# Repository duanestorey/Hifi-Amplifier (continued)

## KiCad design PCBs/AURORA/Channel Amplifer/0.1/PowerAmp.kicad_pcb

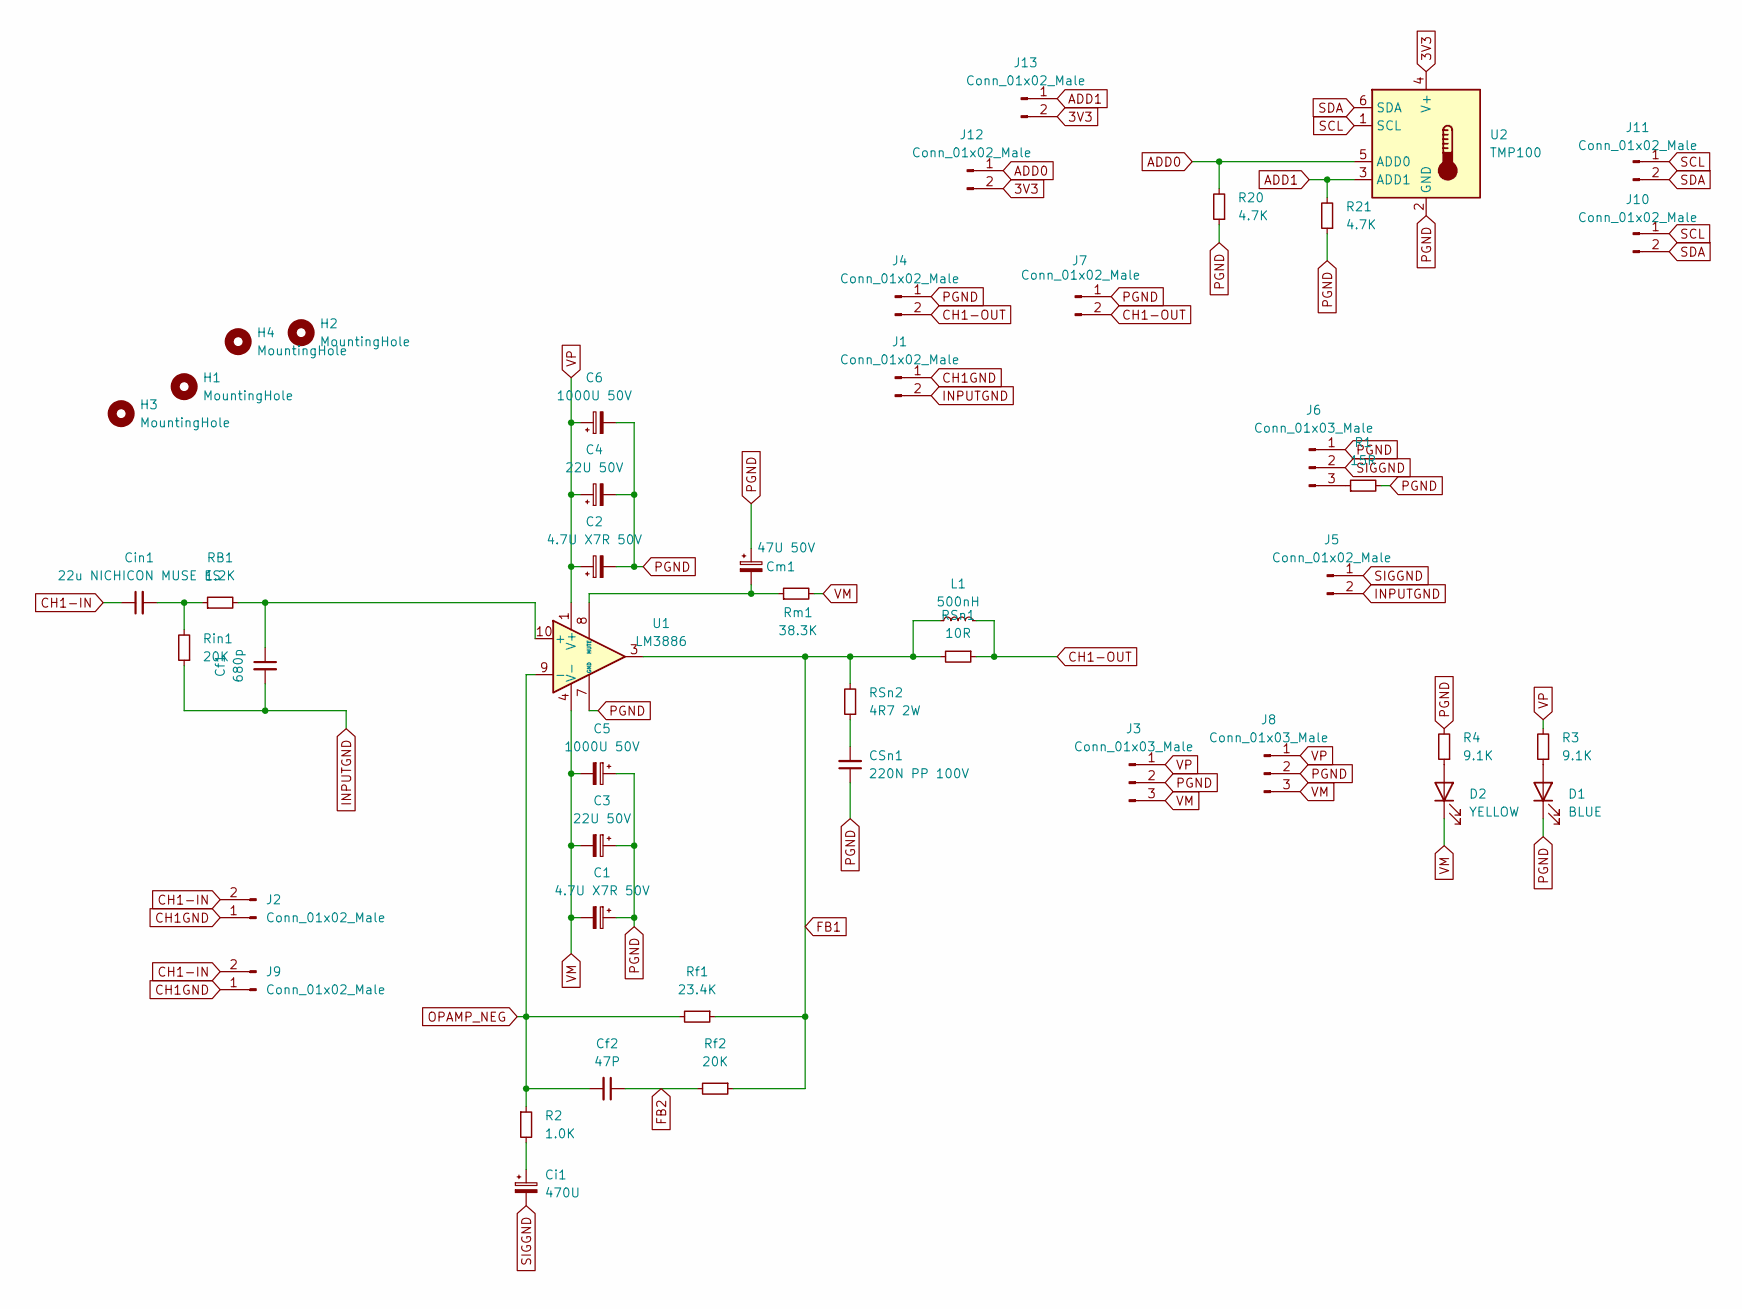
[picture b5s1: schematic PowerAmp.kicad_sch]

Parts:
C1, C2: 4.7U X7R 50V; C_1206_3216Metric_Pad1.33x1.80mm_HandSolder
C3, C4: 22U 50V; CP_Radial_D6.3mm_P2.50mm
C5, C6: 1000U 50V; CP_Radial_D12.5mm_P5.00mm
CSn1: 220N PP 100V; C_Rect_L18.0mm_W7.0mm_P15.00mm_FKS3_FKP3
Cf1: 680p; C_1206_3216Metric_Pad1.33x1.80mm_HandSolder
Cf2: 47P; C_1206_3216Metric_Pad1.33x1.80mm_HandSolder
Ci1: 470U; CP_Radial_D12.5mm_P5.00mm
Cin1: 22u NICHICON MUSE ES; C_Radial_D10.0mm_H12.5mm_P5.00mm
Cm1: 47U 50V; CP_Radial_D6.3mm_P2.50mm
D1: BLUE; LED_0805_2012Metric_Pad1.15x1.40mm_HandSolder
D2: YELLOW; LED_0805_2012Metric_Pad1.15x1.40mm_HandSolder
H1, H2, H3, H4: MountingHole; MountingHole_3mm
J1, J5, J12, J13: Conn_01x02_Male; PinHeader_1x02_P2.54mm_Vertical
J2, J9, J10, J11: Conn_01x02_Male; JST_PH_B2B-PH-K_1x02_P2.00mm_Vertical
J3, J8: Conn_01x03_Male; JST_VH_B3P-VH-B_1x03_P3.96mm_Vertical
J4, J7: Conn_01x02_Male; JST_VH_B2P-VH_1x02_P3.96mm_Vertical
J6: Conn_01x03_Male; PinHeader_1x03_P2.54mm_Vertical
L1: 500nH; 500nH Inductor Aliexpress Air Gap
R1: 15R; R_1206_3216Metric_Pad1.30x1.75mm_HandSolder
R2: 1.0K; R_1206_3216Metric_Pad1.30x1.75mm_HandSolder
R3, R4: 9.1K; R_0805_2012Metric_Pad1.20x1.40mm_HandSolder
R20, R21: 4.7K; R_0603_1608Metric_Pad0.98x0.95mm_HandSolder
RB1: 1.2K; R_1206_3216Metric_Pad1.30x1.75mm_HandSolder
RSn1: 10R; R_4020_10251Metric_Pad1.65x5.30mm_HandSolder
RSn2: 4R7 2W; R_2512_6332Metric_Pad1.40x3.35mm_HandSolder
Rf1: 23.4K; R_1206_3216Metric_Pad1.30x1.75mm_HandSolder
Rf2: 20K; R_1206_3216Metric_Pad1.30x1.75mm_HandSolder
Rin1: 20K; R_1206_3216Metric_Pad1.30x1.75mm_HandSolder
Rm1: 38.3K; R_1206_3216Metric_Pad1.30x1.75mm_HandSolder
U1: LM3886; TO-220-11_P3.4x5.08mm_StaggerOdd_Lead4.85mm_Vertical
U2: TMP100; SOT-23-6

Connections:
3V3: J12.2, J13.2, U2.4 (V+)
ADD0: J12.1, R20.2, U2.5 (ADD0)
ADD1: J13.1, R21.2, U2.3 (ADD1)
CH1-IN: Cin1.1, J2.2, J9.2
CH1-OUT: J4.2, J7.2, L1.2, RSn1.1
CH1GND: J1.1, J2.1, J9.1
FB1: L1.1, RSn1.2, RSn2.2, Rf1.1, Rf2.1, U1.3
FB2: Cf2.1, Rf2.2
INPUTGND: Cf1.2, J1.2, J5.2, Rin1.1
unnamed: CSn1.2, RSn2.1
unnamed: Ci1.1, R2.2
unnamed: Cin1.2, RB1.1, Rin1.2
unnamed: D1.2 (A), R3.1
unnamed: D2.2 (A), R4.1
unnamed: J6.3, R1.1
unnamed: Cf1.1, RB1.2, U1.10 (+)
unnamed: Cm1.2, Rm1.1, U1.8 (MUTE)
OPAMP_NEG: Cf2.2, R2.1, Rf1.2, U1.9 (-)
PGND: C1.1, C2.2, C3.1, C4.2, C5.1, C6.2, CSn1.1, Cm1.1, D1.1 (K), J3.2, J4.1, J6.1, J7.1, J8.2, R1.2, R4.2, R20.1, R21.1, U1.7 (GND), U2.2 (GND)
SCL: J10.1, J11.1, U2.1 (SCL)
SDA: J10.2, J11.2, U2.6 (SDA)
SIGGND: Ci1.2, J5.1, J6.2
VM: C1.2, C3.2, C5.2, D2.1 (K), J3.3, J8.3, Rm1.2, U1.4 (V-)
VP: C2.1, C4.1, C6.1, J3.1, J8.1, R3.2, U1.1 (V+), U1.5 (V+)

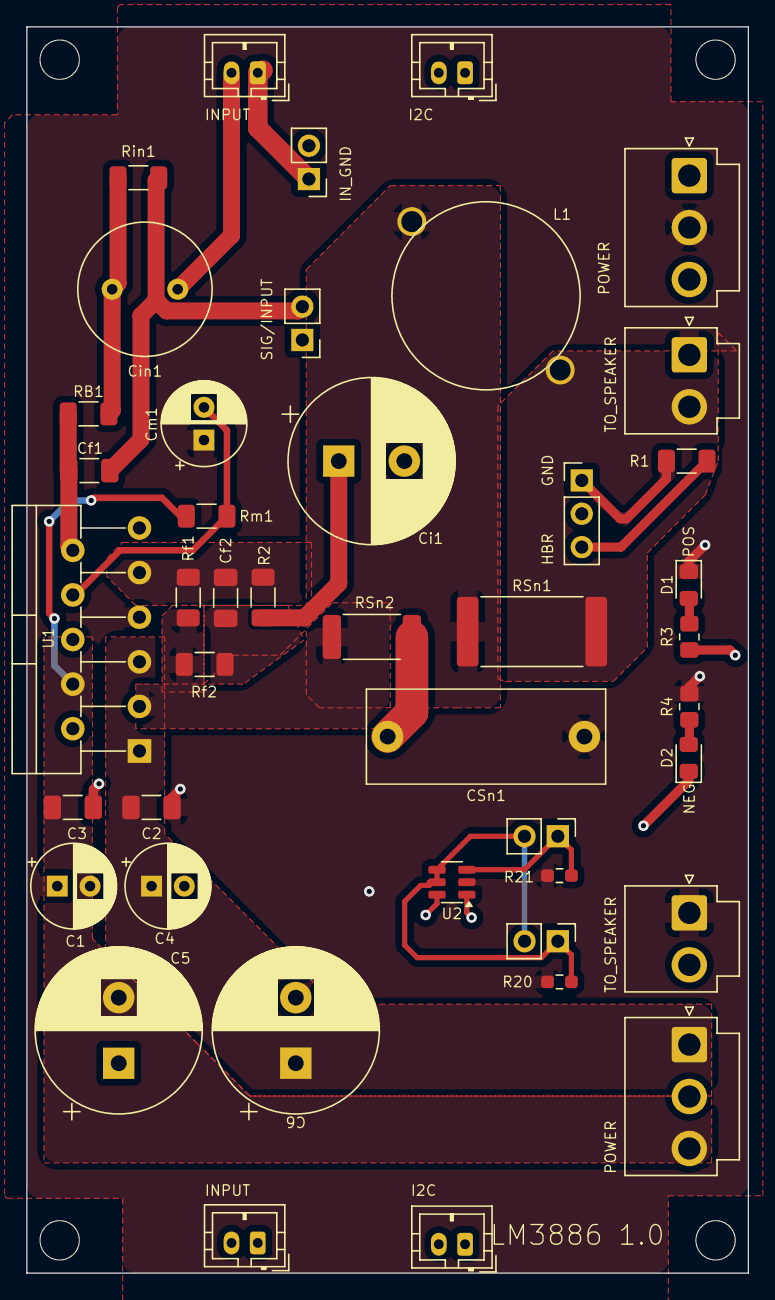
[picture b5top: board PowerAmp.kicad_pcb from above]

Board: 4 copper layers, 55.0 x 95.0 mm, 47 parts (0 on the bottom side), 24 nets.

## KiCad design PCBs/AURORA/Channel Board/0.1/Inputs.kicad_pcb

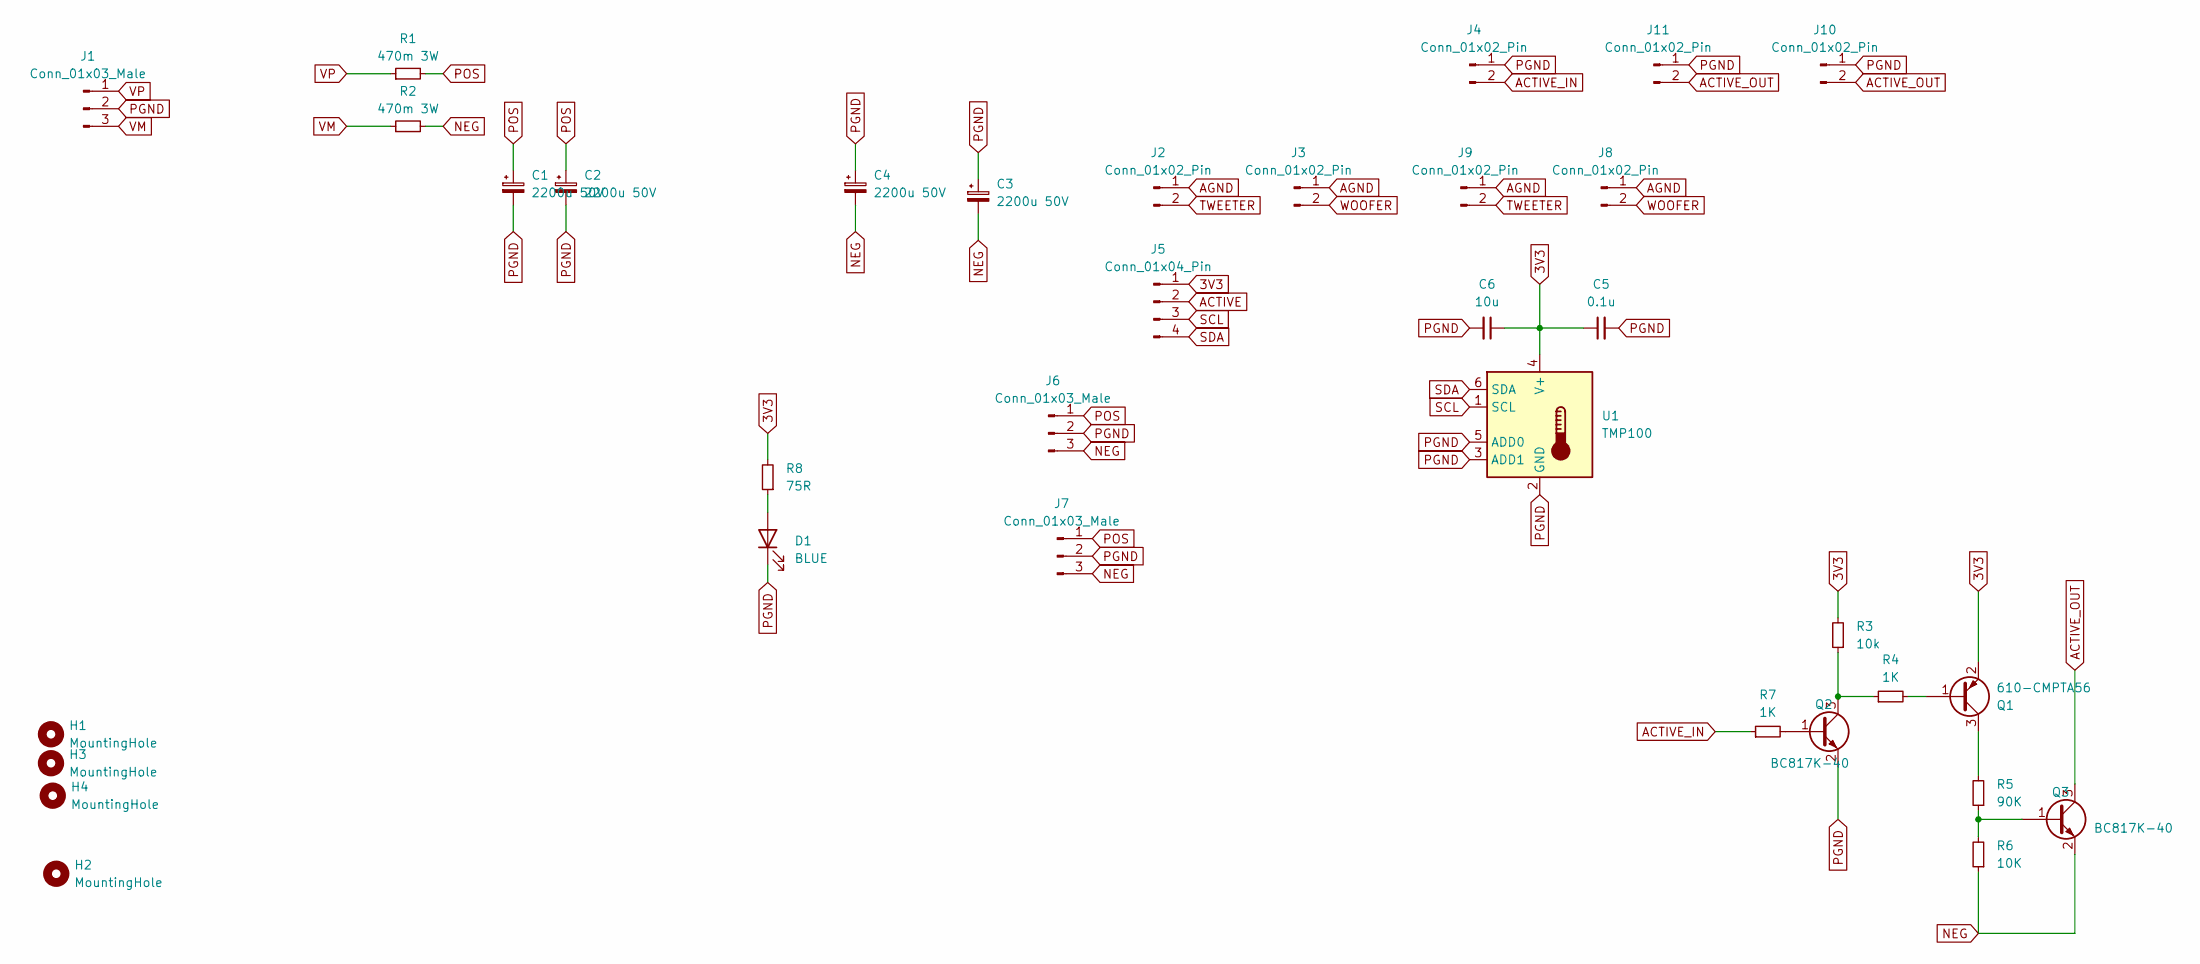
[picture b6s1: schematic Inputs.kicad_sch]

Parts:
C1, C2, C3, C4: 2200u 50V; CP_Radial_D16.0mm_P7.50mm
C5: 0.1u; C_0805_2012Metric_Pad1.18x1.45mm_HandSolder
C6: 10u; C_1206_3216Metric_Pad1.33x1.80mm_HandSolder
D1: BLUE; LED_0805_2012Metric
H1, H2, H3, H4: MountingHole; MountingHole_3.2mm_M3
J1, J6, J7: Conn_01x03_Male; JST_VH_B3P-VH-B_1x03_P3.96mm_Vertical
J2, J3, J4, J8, J9, J10, J11: Conn_01x02_Pin; JST_PH_B2B-PH-K_1x02_P2.00mm_Vertical
J5: Conn_01x04_Pin; JST_PH_B4B-PH-K_1x04_P2.00mm_Vertical
Q1: 610-CMPTA56; TSOT-23
Q2, Q3: BC817K-40; TSOT-23
R1, R2: 470m 3W; R_1218_3246Metric_Pad1.22x4.75mm_HandSolder; Mouser RLW73PA3FR47TDF
R3: 10k; R_0603_1608Metric_Pad0.98x0.95mm_HandSolder
R4, R7: 1K; R_0603_1608Metric_Pad0.98x0.95mm_HandSolder
R5: 90K; R_0603_1608Metric_Pad0.98x0.95mm_HandSolder
R6: 10K; R_0603_1608Metric_Pad0.98x0.95mm_HandSolder
R8: 75R; R_0603_1608Metric_Pad0.98x0.95mm_HandSolder
U1: TMP100; SOT-23-6

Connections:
3V3: C5.1, C6.1, J5.1, Q1.2 (E), R3.2, R8.2, U1.4 (V+)
ACTIVE: J5.2
ACTIVE_IN: J4.2, R7.1
ACTIVE_OUT: J10.2, J11.2, Q3.3 (C)
AGND: J2.1, J3.1, J8.1, J9.1
NEG: C3.2, C4.2, J6.3, J7.3, Q3.2 (E), R2.2, R6.1
unnamed: D1.2 (A), R8.1
unnamed: Q1.1 (B), R4.2
unnamed: Q1.3 (C), R5.2
unnamed: Q2.1 (B), R7.2
unnamed: Q2.3 (C), R3.1, R4.1
unnamed: Q3.1 (B), R5.1, R6.2
PGND: C1.2, C2.2, C3.1, C4.1, C5.2, C6.2, D1.1 (K), J1.2, J4.1, J6.2, J7.2, J10.1, J11.1, Q2.2 (E), U1.2 (GND), U1.3 (ADD1), U1.5 (ADD0)
POS: C1.1, C2.1, J6.1, J7.1, R1.2
SCL: J5.3, U1.1 (SCL)
SDA: J5.4, U1.6 (SDA)
TWEETER: J2.2, J9.2
VM: J1.3, R2.1
VP: J1.1, R1.1
WOOFER: J3.2, J8.2

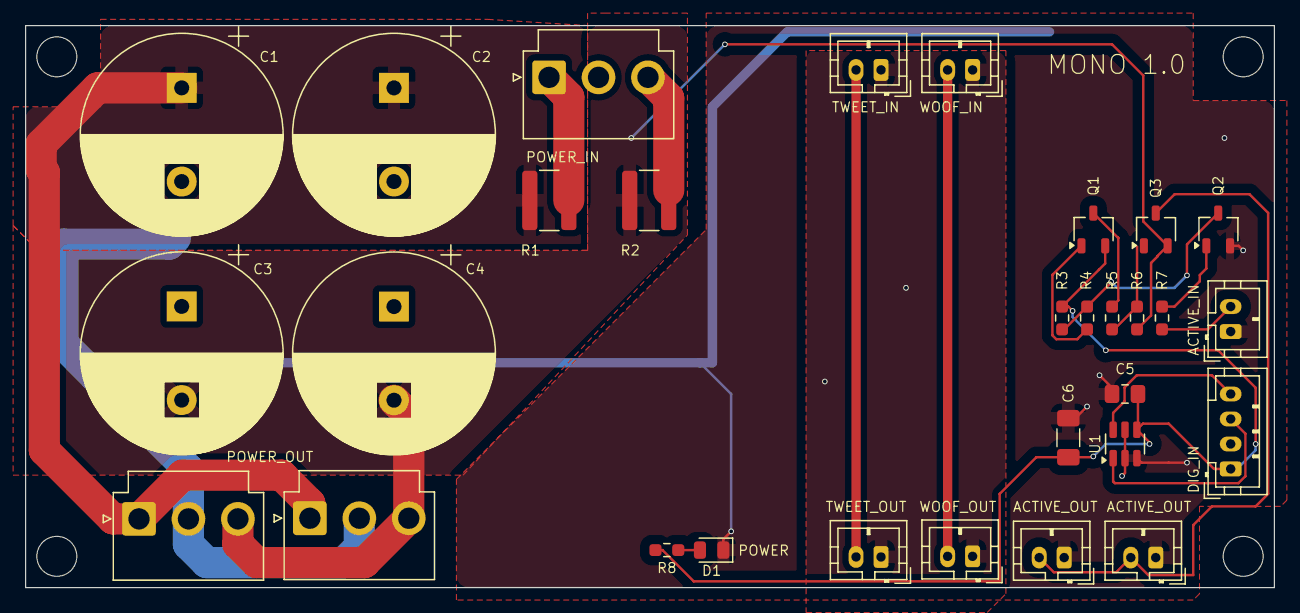
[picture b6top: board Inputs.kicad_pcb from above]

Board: 2 copper layers, 100.0 x 45.0 mm, 34 parts (0 on the bottom side), 19 nets.

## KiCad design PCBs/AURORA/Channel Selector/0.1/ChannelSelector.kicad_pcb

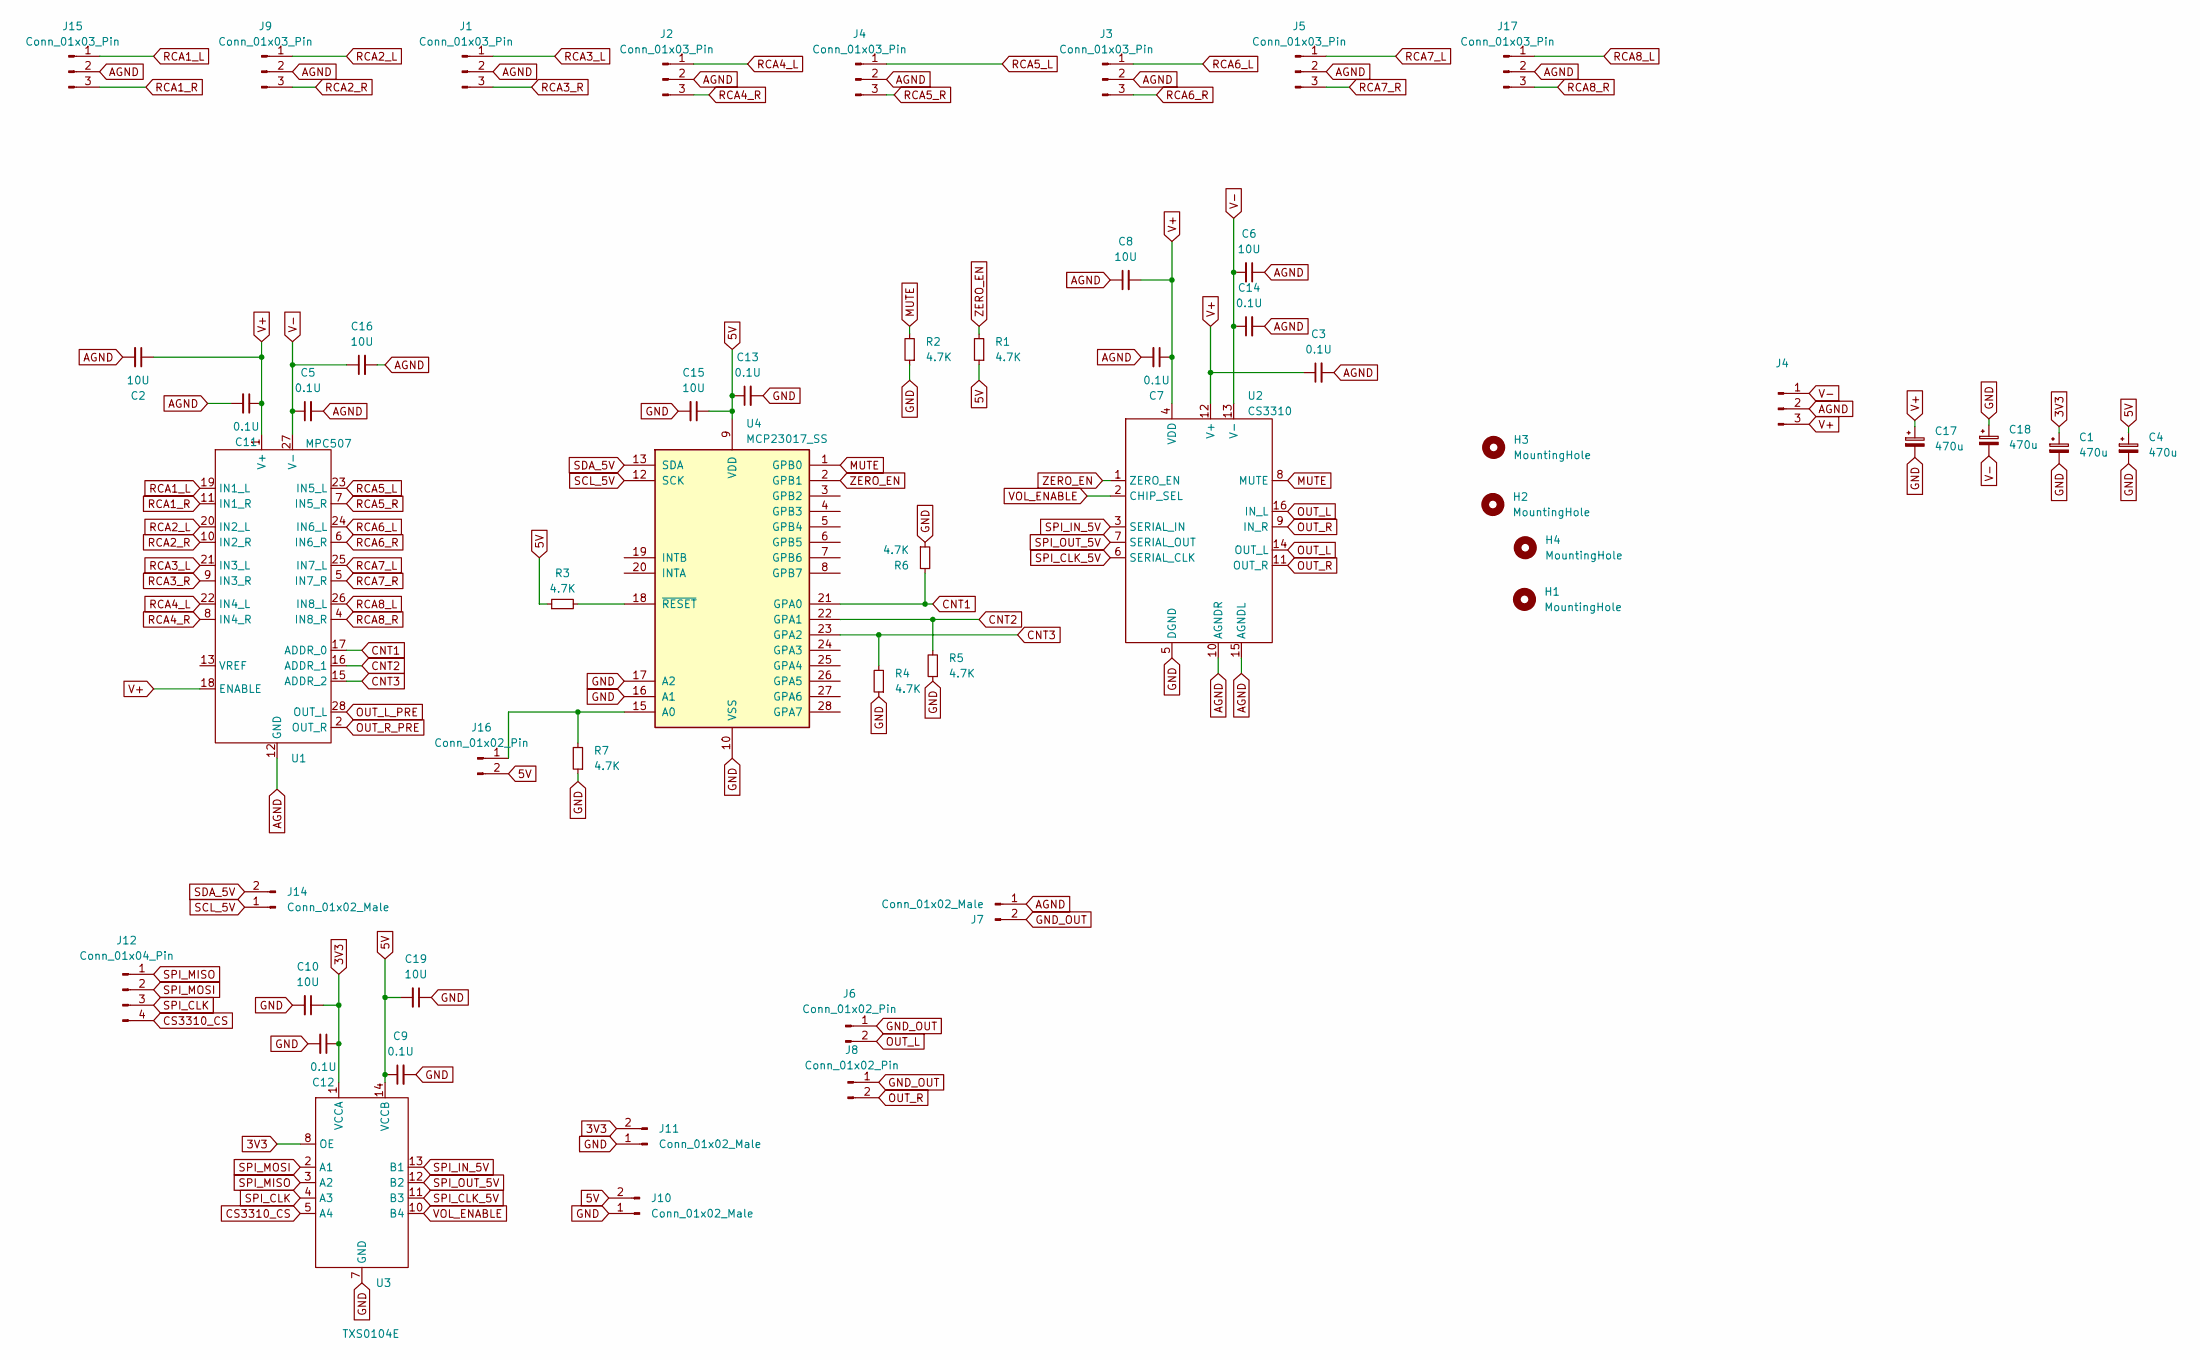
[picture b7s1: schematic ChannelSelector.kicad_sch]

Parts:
C1, C4, C17, C18: 470u; CP_Radial_D6.3mm_P2.50mm
C2, C6, C8, C10, C15, C16, C19: 10U; C_1206_3216Metric_Pad1.33x1.80mm_HandSolder
C3, C5, C7, C9, C11, C12, C13, C14: 0.1U; C_0805_2012Metric_Pad1.18x1.45mm_HandSolder
H1, H2, H3, H4: MountingHole; MountingHole_3.2mm_M3
J1, J2, J3, J4, J5, J9, J15: Conn_01x03_Pin; JST_PH_B3B-PH-K_1x03_P2.00mm_Vertical
J6, J8: Conn_01x02_Pin; JST_PH_B2B-PH-K_1x02_P2.00mm_Vertical
J7: Conn_01x02_Male; PinHeader_1x02_P2.54mm_Vertical
J10, J11, J14: Conn_01x02_Male; JST_PH_B2B-PH-K_1x02_P2.00mm_Vertical
J12: Conn_01x04_Pin; JST_PH_B4B-PH-K_1x04_P2.00mm_Vertical
J16: Conn_01x02_Pin; PinHeader_1x02_P2.54mm_Vertical
J17: Conn_01x03_Pin; PinHeader_1x03_P2.54mm_Vertical
R1, R2, R3, R4, R5, R6, R7: 4.7K; R_0603_1608Metric_Pad0.98x0.95mm_HandSolder
U1: MPC507; SOIC-28W_7.5x18.7mm_P1.27mm
U2: CS3310; SOIC-16W_7.5x10.3mm_P1.27mm
U3: TXS0104E; TSSOP-14_4.4x5mm_P0.65mm
U4: MCP23017_SS; SSOP-28_5.3x10.2mm_P0.65mm

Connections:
3V3: C1.1, C10.1, C12.1, J11.2, U3.1 (VCCA), U3.8 (OE)
5V: C4.1, C9.1, C13.1, C15.1, C19.2, J10.2, J16.2, R1.1, R3.1, U3.14 (VCCB), U4.9 (VDD)
AGND: C2.2, C3.2, C5.2, C6.1, C7.2, C8.1, C11.2, C14.2, C16.2, J1.2, J2.2, J3.2, J4.2, J5.2, J7.1, J9.2, J15.2, J17.2, U1.12 (GND), U2.10 (AGNDR), U2.15 (AGNDL); also elsewhere on the board
CNT1: R6.2, U1.17 (ADDR_0), U4.21 (GPA0)
CNT2: R5.2, U1.16 (ADDR_1), U4.22 (GPA1)
CNT3: R4.2, U1.15 (ADDR_2), U4.23 (GPA2)
CS3310_CS: J12.4, U3.5 (A4)
GND: C1.2, C4.2, C9.2, C10.2, C12.2, C13.2, C15.2, C17.2, C18.1, C19.1, J10.1, J11.1, R2.1, R4.1, R5.1, R6.1, R7.1, U2.5 (DGND), U3.7 (GND), U4.10 (VSS), U4.16 (A1), U4.17 (A2)
GND_OUT: J6.1, J7.2, J8.1
MUTE: R2.2, U2.8 (MUTE), U4.1 (GPB0)
unnamed: J16.1, R7.2, U4.15 (A0)
unnamed: R3.2, U4.18 (~RESET)
OUT_L: J6.2, U2.14 (OUT_L), U2.16 (IN_L)
OUT_L_PRE: U1.28 (OUT_L)
OUT_R: J8.2, U2.9 (IN_R), U2.11 (OUT_R)
OUT_R_PRE: U1.2 (OUT_R)
RCA1_L: J15.1, U1.19 (IN1_L)
RCA1_R: J15.3, U1.11 (IN1_R)
RCA2_L: J9.1, U1.20 (IN2_L)
RCA2_R: J9.3, U1.10 (IN2_R)
RCA3_L: J1.1, U1.21 (IN3_L)
RCA3_R: J1.3, U1.9 (IN3_R)
RCA4_L: J2.1, U1.22 (IN4_L)
RCA4_R: J2.3, U1.8 (IN4_R)
RCA6_L: J3.1, U1.24 (IN6_L)
RCA6_R: J3.3, U1.6 (IN6_R)
RCA7_L: J5.1, U1.25 (IN7_L)
RCA7_R: J5.3, U1.5 (IN7_R)
RCA8_L: J17.1, U1.26 (IN8_L)
RCA8_R: J17.3, U1.4 (IN8_R)
SCL_5V: J14.1, U4.12 (SCK)
SDA_5V: J14.2, U4.13 (SDA)
SPI_CLK: J12.3, U3.4 (A3)
SPI_CLK_5V: U2.6 (SERIAL_CLK), U3.11 (B3)
SPI_IN_5V: U2.3 (SERIAL_IN), U3.13 (B1)
SPI_MISO: J12.1, U3.3 (A2)
SPI_MOSI: J12.2, U3.2 (A1)
SPI_OUT_5V: U2.7 (SERIAL_OUT), U3.12 (B2)
VOL_ENABLE: U2.2 (CHIP_SEL), U3.10 (B4)
ZERO_EN: R1.2, U2.1 (ZERO_EN), U4.2 (GPB1)

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
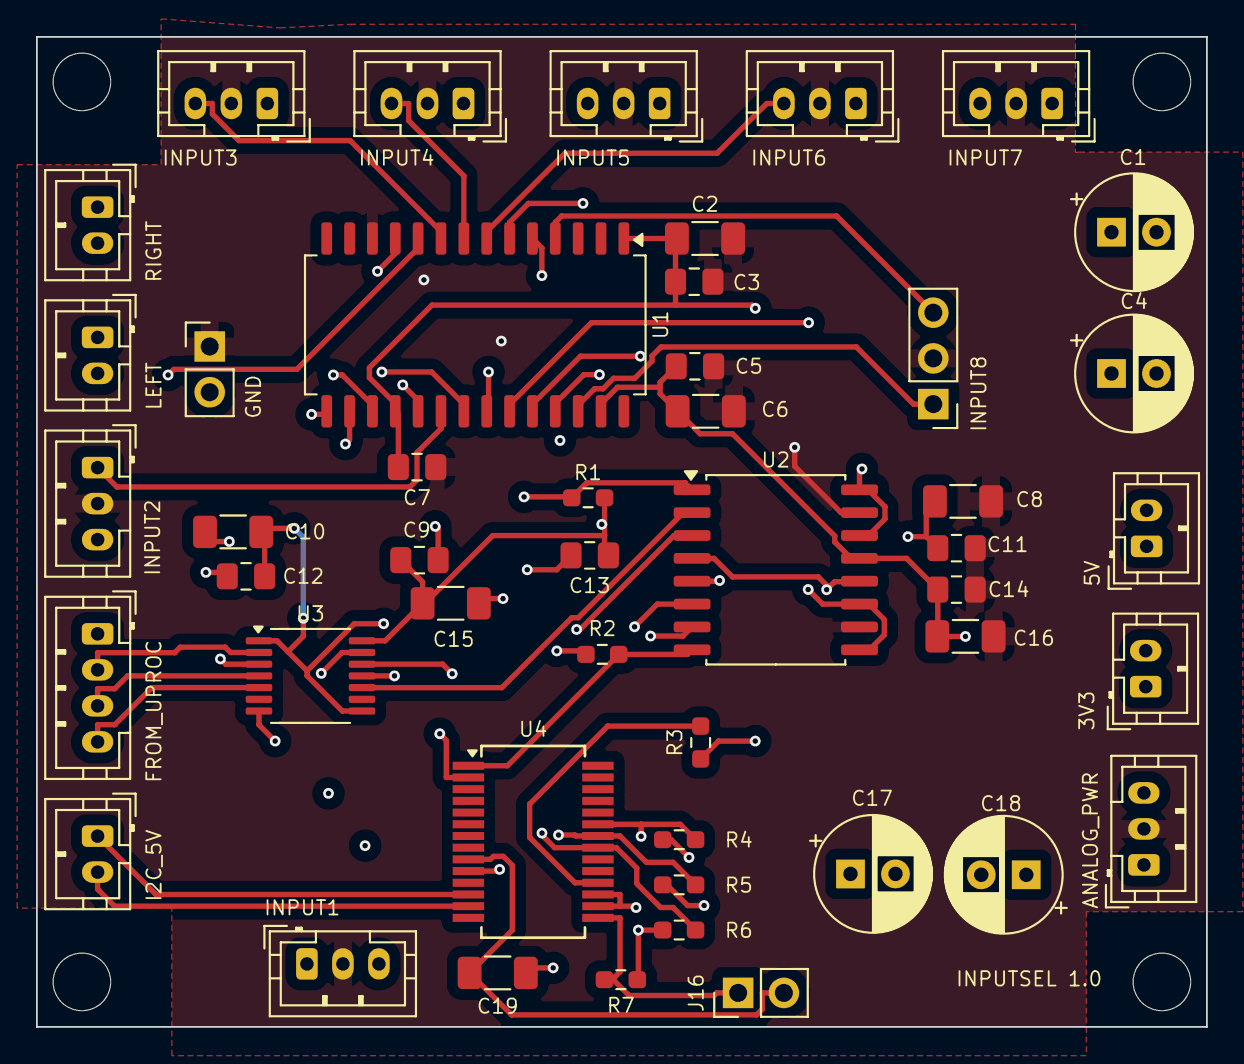
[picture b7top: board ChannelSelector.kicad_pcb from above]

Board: 4 copper layers, 65.0 x 55.0 mm, 51 parts (0 on the bottom side), 42 nets.

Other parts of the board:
J13: Conn_01x03_Male; JST_PH_B3B-PH-K_1x03_P2.00mm_Vertical

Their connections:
AGND: J13.2; also elsewhere on the board

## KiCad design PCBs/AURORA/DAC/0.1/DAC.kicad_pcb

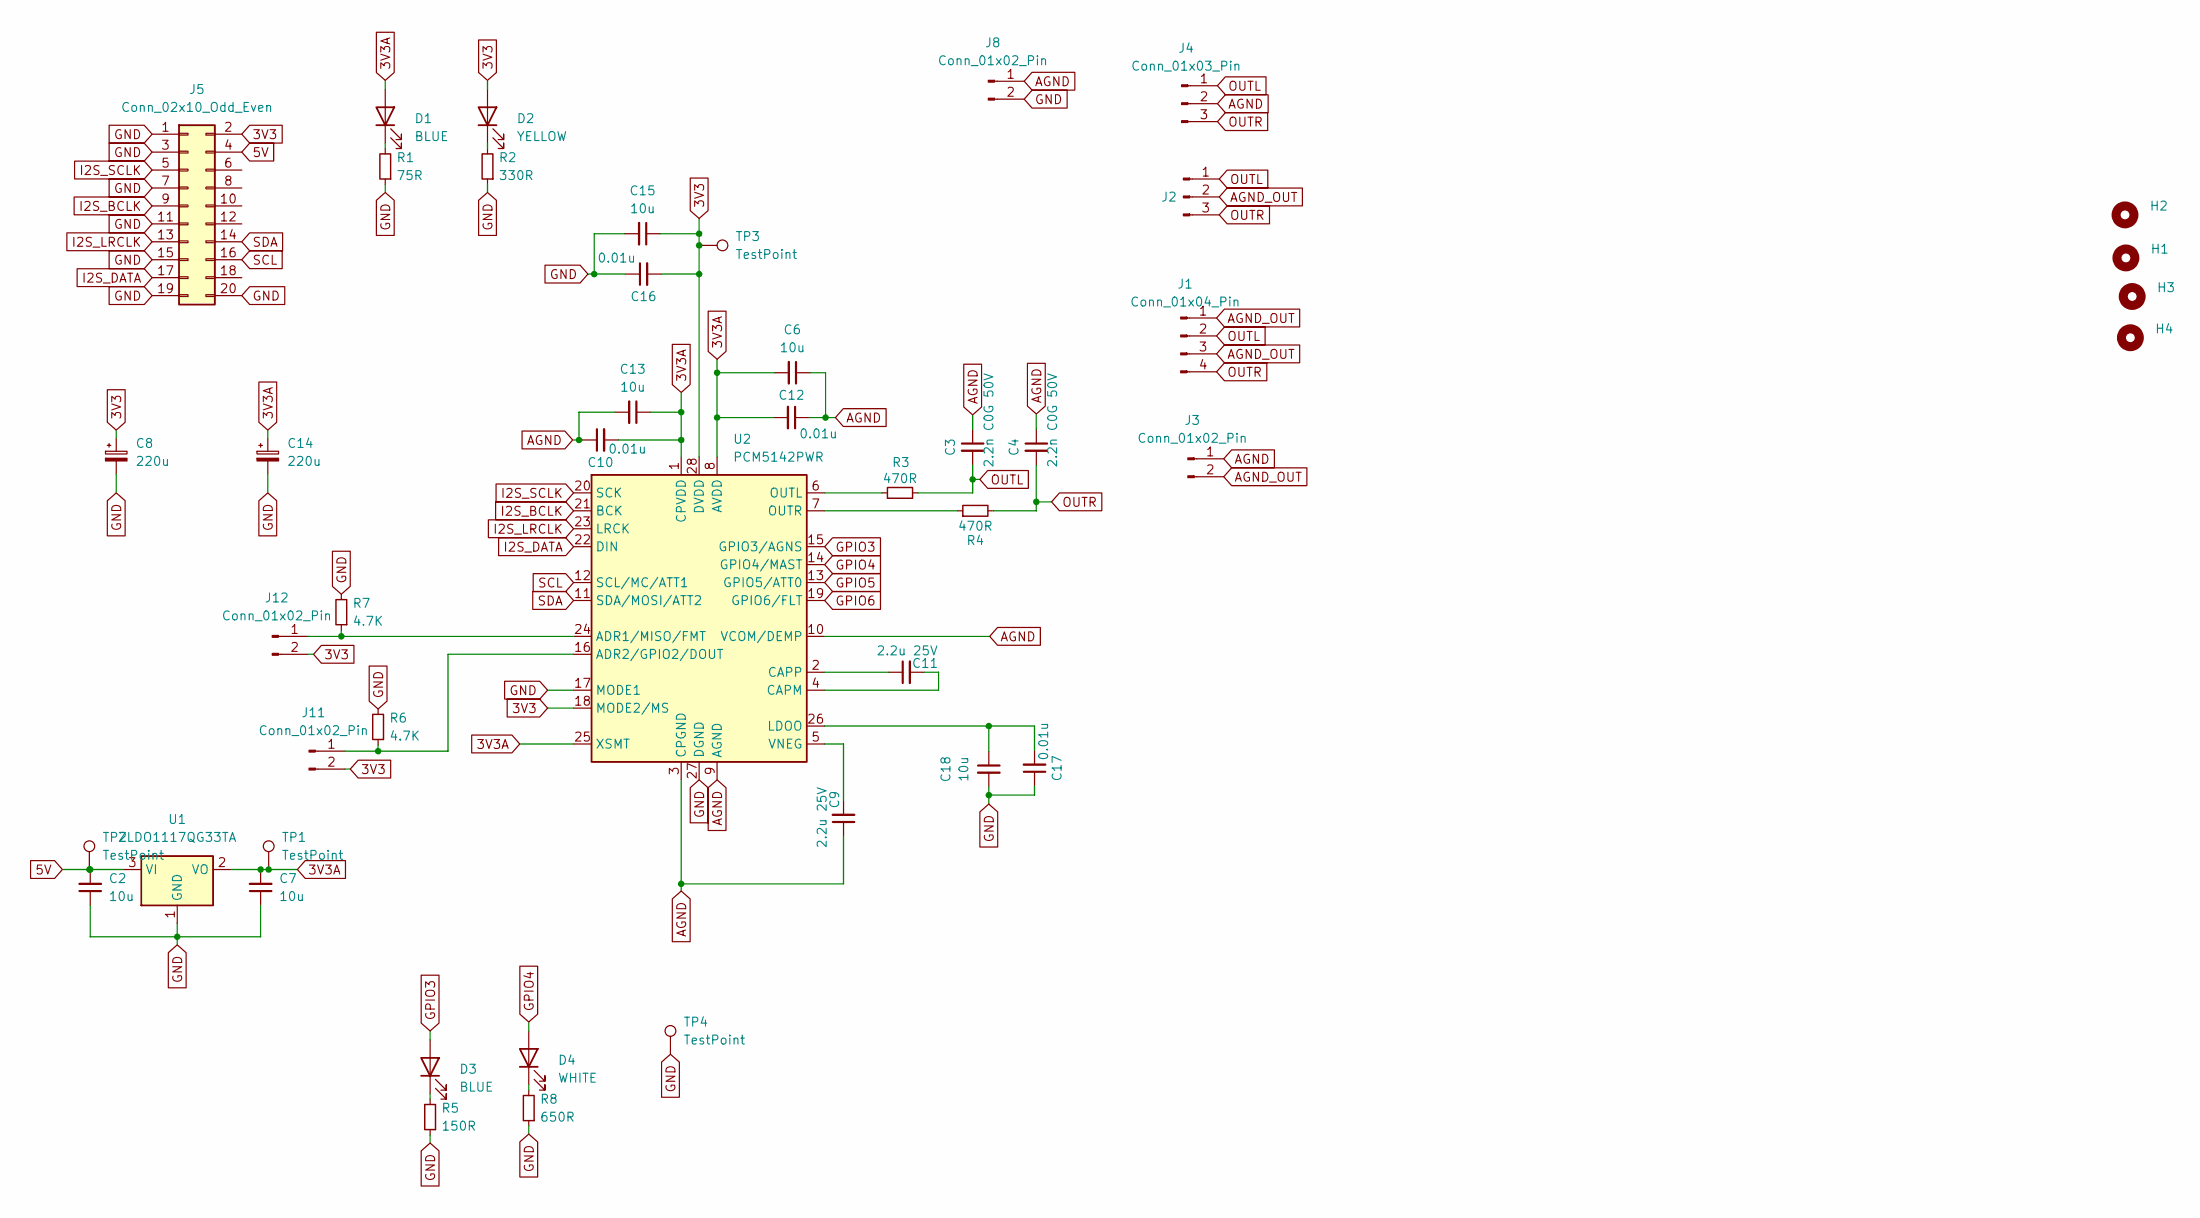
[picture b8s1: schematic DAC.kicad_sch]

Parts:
C2, C6, C7, C13, C15, C18: 10u; C_1206_3216Metric_Pad1.33x1.80mm_HandSolder
C3, C4: 2.2n C0G 50V; C_Rect_L4.6mm_W3.0mm_P2.50mm_MKS02_FKP02
C8, C14: 220u; CP_Radial_D6.3mm_P2.50mm
C9, C11: 2.2u 25V; C_0805_2012Metric
C10, C12, C16, C17: 0.01u; C_0805_2012Metric
D1, D3: BLUE; LED_0805_2012Metric_Pad1.15x1.40mm_HandSolder
D2: YELLOW; LED_0805_2012Metric_Pad1.15x1.40mm_HandSolder
D4: WHITE; LED_0805_2012Metric_Pad1.15x1.40mm_HandSolder
H1, H2, H3, H4: MountingHole; MountingHole_3.2mm_M3
J1: Conn_01x04_Pin; JST_PH_B4B-PH-K_1x04_P2.00mm_Vertical
J2: Conn_01x03_Pin; JST_PH_B3B-PH-K_1x03_P2.00mm_Vertical
J3, J8, J11, J12: Conn_01x02_Pin; PinHeader_1x02_P2.54mm_Vertical
J4: Conn_01x03_Pin; PinHeader_1x03_P2.54mm_Vertical
J5: Conn_02x10_Odd_Even; PinHeader_2x10_P2.54mm_Vertical
R1: 75R; R_0603_1608Metric_Pad0.98x0.95mm_HandSolder
R2: 330R; R_0603_1608Metric_Pad0.98x0.95mm_HandSolder
R3, R4: 470R; R_1206_3216Metric_Pad1.30x1.75mm_HandSolder
R5: 150R; R_0603_1608Metric_Pad0.98x0.95mm_HandSolder
R6, R7: 4.7K; R_0603_1608Metric_Pad0.98x0.95mm_HandSolder
R8: 650R; R_0603_1608Metric_Pad0.98x0.95mm_HandSolder
TP1, TP2, TP3, TP4: TestPoint; TestPoint_Pad_2.0x2.0mm
U1: ZLDO1117QG33TA; SOT-223-3_TabPin2
U2: PCM5142PWR; TSSOP-28_4.4x9.7mm_P0.65mm

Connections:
3V3: C8.1, C15.1, C16.2, D2.2 (A), J5.2, J11.2, J12.2, TP3.1, U2.18 (MODE2/MS), U2.28 (DVDD)
3V3A: C6.2, C7.2, C10.2, C12.2, C13.1, C14.1, D1.2 (A), TP1.1, U1.2 (VO), U2.1 (CPVDD), U2.8 (AVDD), U2.25 (XSMT)
5V: C2.2, J5.4, TP2.1, U1.3 (VI)
AGND: C3.1, C4.1, C6.1, C9.1, C10.1, C12.1, C13.2, J3.1, J4.2, J8.1, U2.3 (CPGND), U2.9 (AGND), U2.10 (VCOM/DEMP)
AGND_OUT: J1.1, J1.3, J2.2, J3.2
GND: C2.1, C7.1, C8.2, C14.2, C15.2, C16.1, C17.1, C18.2, J5.1, J5.3, J5.7, J5.11, J5.15, J5.19, J5.20, J8.2, R1.1, R2.1, R5.1, R6.2, R7.2, R8.1, TP4.1, U1.1 (GND), U2.17 (MODE1), U2.27 (DGND)
GPIO3: D3.2 (A), U2.15 (GPIO3/AGNS)
GPIO4: D4.2 (A), U2.14 (GPIO4/MAST)
GPIO5: U2.13 (GPIO5/ATT0)
GPIO6: U2.19 (GPIO6/FLT)
I2S_BCLK: J5.9, U2.21 (BCK)
I2S_DATA: J5.17, U2.22 (DIN)
I2S_LRCLK: J5.13, U2.23 (LRCK)
I2S_SCLK: J5.5, U2.20 (SCK)
unnamed: D1.1 (K), R1.2
unnamed: D2.1 (K), R2.2
unnamed: D3.1 (K), R5.2
unnamed: D4.1 (K), R8.2
unnamed: J11.1, R6.1, U2.16 (ADR2/GPIO2/DOUT)
unnamed: J12.1, R7.1, U2.24 (ADR1/MISO/FMT)
unnamed: C11.2, U2.4 (CAPM)
unnamed: C11.1, U2.2 (CAPP)
unnamed: C17.2, C18.1, U2.26 (LDOO)
unnamed: R3.1, U2.6 (OUTL)
unnamed: R4.1, U2.7 (OUTR)
unnamed: C9.2, U2.5 (VNEG)
OUTL: C3.2, J1.2, J2.1, J4.1, R3.2
OUTR: C4.2, J1.4, J2.3, J4.3, R4.2
SCL: J5.16, U2.12 (SCL/MC/ATT1)
SDA: J5.14, U2.11 (SDA/MOSI/ATT2)

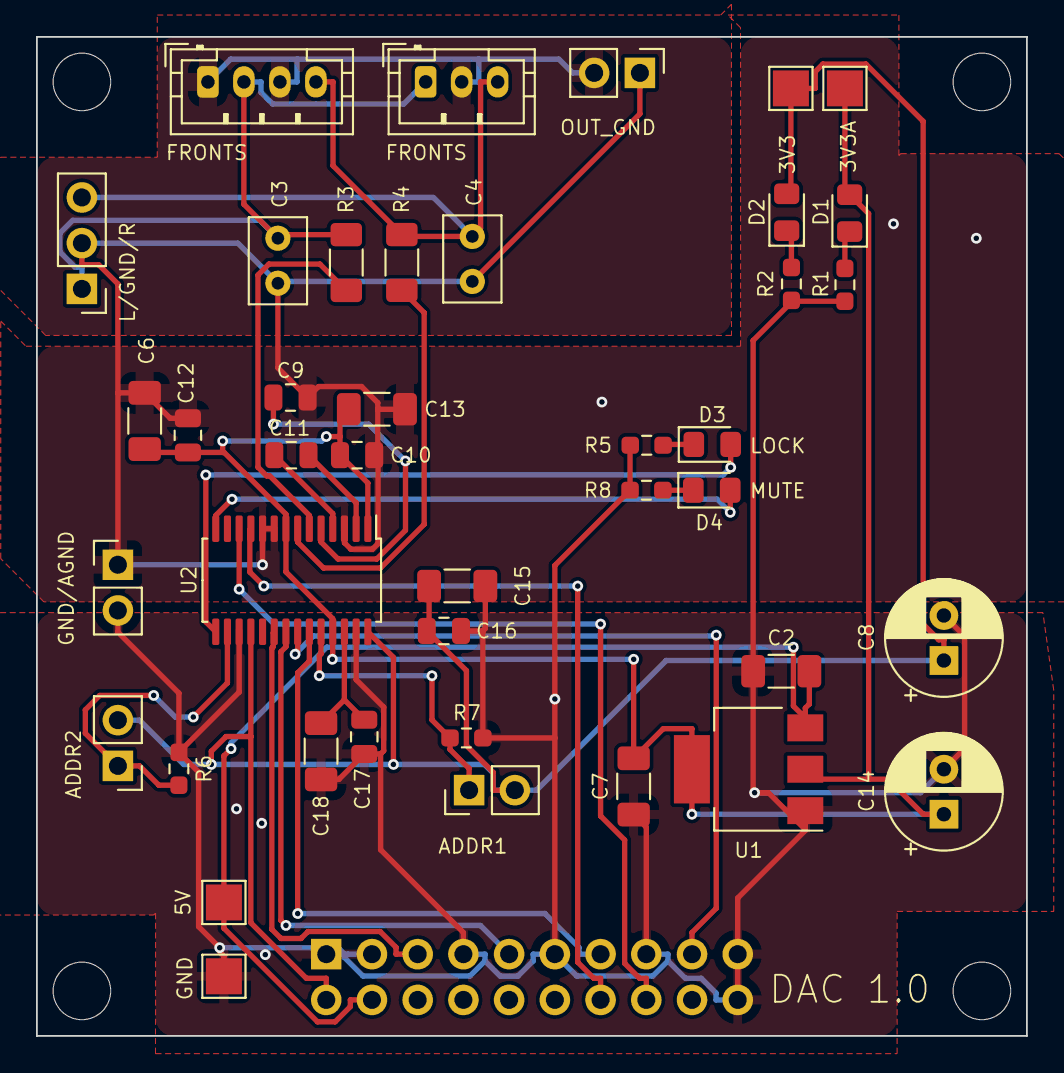
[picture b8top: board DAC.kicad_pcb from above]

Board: 4 copper layers, 55.0 x 55.5 mm, 46 parts (1 on the bottom side), 28 nets.
